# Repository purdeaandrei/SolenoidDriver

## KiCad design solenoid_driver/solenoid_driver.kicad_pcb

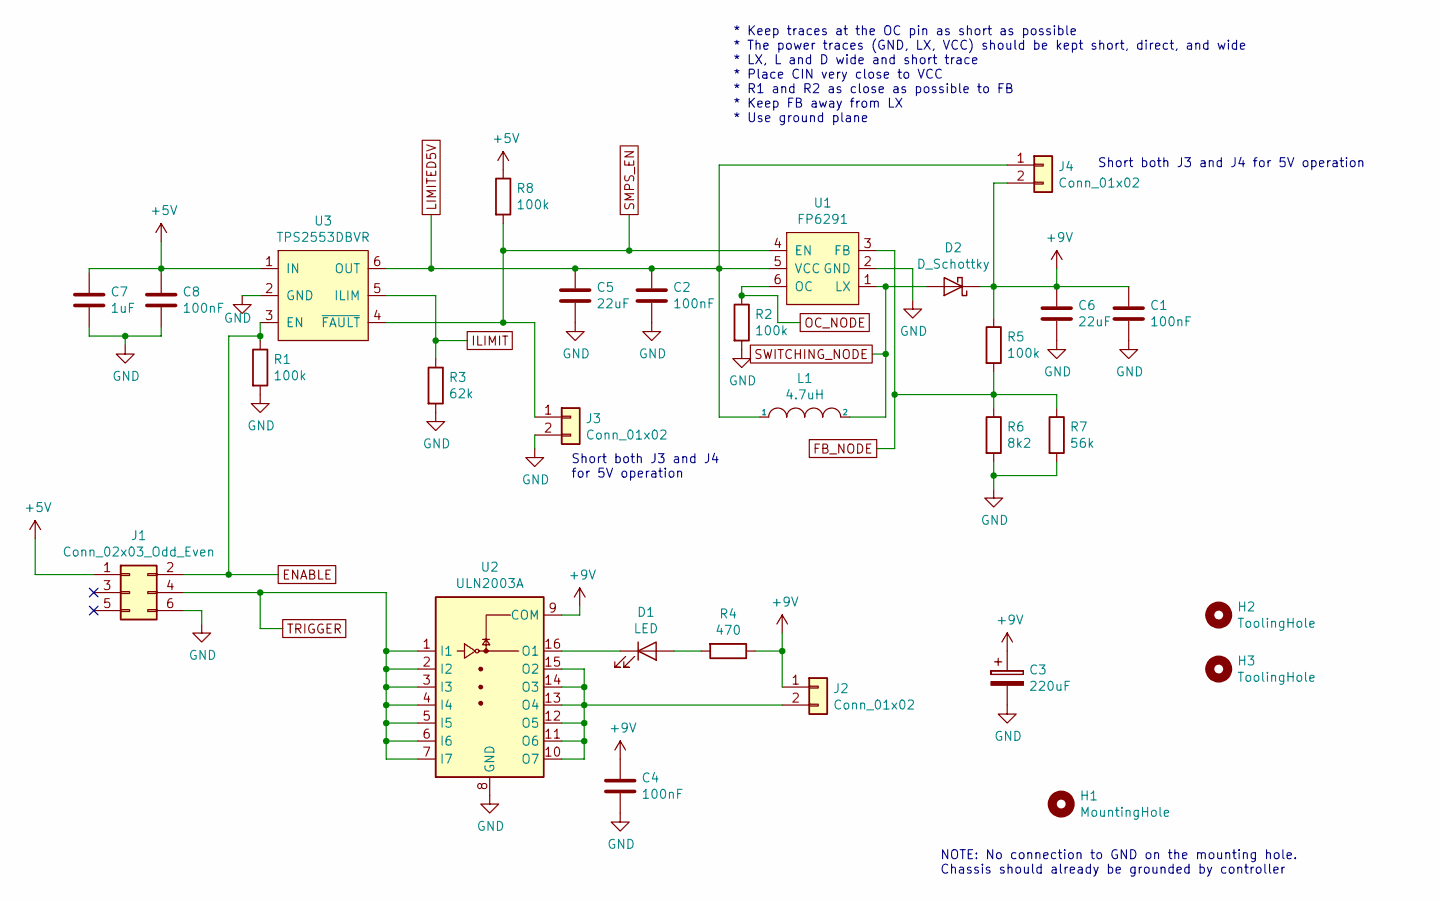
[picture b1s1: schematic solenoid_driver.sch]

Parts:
C1, C2, C4, C8: 100nF; C_0805_2012Metric_Pad1.15x1.40mm_HandSolder; LCSC C49678
C3: 220uF; CP_Elec_6.3x7.7; LCSC C127327
C5, C6: 22uF; C_0805_2012Metric_Pad1.15x1.40mm_HandSolder; LCSC C45783
C7: 1uF; C_0805_2012Metric_Pad1.15x1.40mm_HandSolder; LCSC C28323
D1: LED; LED_0805_2012Metric_Pad1.15x1.40mm_HandSolder; LCSC C2296
D2: D_Schottky; D_SMA; LCSC C2480
H1: MountingHole; MountingHole_4mm_Pad
H2, H3: ToolingHole; tooling_hole
J1: Conn_02x03_Odd_Even; PinHeader_2x03_P2.54mm_Vertical
J2: Conn_01x02; PinHeader_1x02_P2.54mm_Vertical
J3, J4: Conn_01x02; shortable
L1: 4.7uH; footprint_for_MWSA0402_HANDSOLD; LCSC C408337
R1, R2, R5, R8: 100k; R_0805_2012Metric_Pad1.15x1.40mm_HandSolder; LCSC C17407
R3: 62k; R_0805_2012Metric_Pad1.15x1.40mm_HandSolder; LCSC C17783
R4: 470; R_0805_2012Metric_Pad1.15x1.40mm_HandSolder; LCSC C17710
R6: 8k2; R_0805_2012Metric_Pad1.15x1.40mm_HandSolder; LCSC C17828
R7: 56k; R_0805_2012Metric_Pad1.15x1.40mm_HandSolder; LCSC C17756
U1: FP6291; SOT-23-6_Handsoldering; LCSC C18701
U2: ULN2003A; SOIC-16_3.9x9.9mm_P1.27mm; LCSC C7512
U3: TPS2553DBVR; SOT-23-6_Handsoldering; LCSC C55266

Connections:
+5V: C7.1, C8.1, J1.1, R8.1, U3.1 (IN)
+9V: C1.1, C3.1, C4.1, C6.1, D2.1 (K), J2.1, J4.2, R4.1, R5.1, U2.9 (COM)
ENABLE: J1.2, R1.1, U3.3 (EN)
FB_NODE: R5.2, R6.1, R7.1, U1.3 (FB)
GND: C1.2, C2.2, C3.2, C4.2, C5.2, C6.2, C7.2, C8.2, J1.6, J3.2, R1.2, R2.2, R3.2, R6.2, R7.2, U1.2 (GND), U2.8 (GND), U3.2 (GND)
ILIMIT: R3.1, U3.5 (ILIM)
LIMITED5V: C2.1, C5.1, J4.1, L1.1, U1.5 (VCC), U3.6 (OUT)
unnamed: D1.1 (K), U2.16 (O1)
unnamed: D1.2 (A), R4.2
unnamed: J2.2, U2.10 (O7), U2.11 (O6), U2.12 (O5), U2.13 (O4), U2.14 (O3), U2.15 (O2)
OC_NODE: R2.1, U1.6 (OC)
SMPS_EN: J3.1, R8.2, U1.4 (EN), U3.4 (~FAULT)
SWITCHING_NODE: D2.2 (A), L1.2, U1.1 (LX)
TRIGGER: J1.4, U2.1 (I1), U2.2 (I2), U2.3 (I3), U2.4 (I4), U2.5 (I5), U2.6 (I6), U2.7 (I7)

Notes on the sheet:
* Keep traces at the OC pin as short as possible * The power traces (GND, LX, VCC) should be kept short, direct, and wide * LX, L and D wide and short trace * Place CIN very close to VCC * R1 and R2 as close as possible to FB * Keep FB away from LX * Use ground plane
NOTE: No connection to GND on the mounting hole. Chassis should already be grounded by controller
Short both J3 and J4 for 5V operation
Short both J3 and J4 for 5V operation

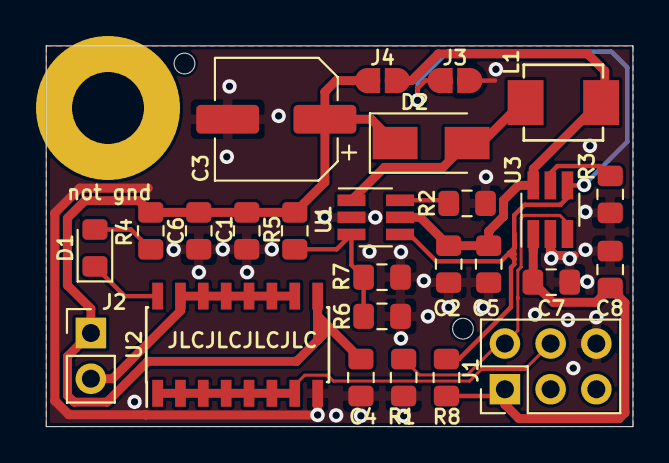
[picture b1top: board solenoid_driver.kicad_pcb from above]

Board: 2 copper layers, 32.6 x 21.1 mm, 29 parts (0 on the bottom side), 14 nets.

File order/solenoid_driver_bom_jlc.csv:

"Comment","Designator","Footprint","LCSC Part #"
"100nF","C2,C4,C1,C8","C_0805_2012Metric_Pad1.15x1.40mm_HandSolder","C49678"
"220uF","C3","CP_Elec_6.3x7.7","C127327"
"22uF","C5,C6","C_0805_2012Metric_Pad1.15x1.40mm_HandSolder","C45783"
"1uF","C7","C_0805_2012Metric_Pad1.15x1.40mm_HandSolder","C28323"
"LED","D1","LED_0805_2012Metric_Pad1.15x1.40mm_HandSolder","C2296"
"D_Schottky","D2","D_SMA","C2480"
"4.7uH","L1","footprint_for_MWSA0402_HANDSOLD","C408337"
"100k","R1,R5,R2,R8","R_0805_2012Metric_Pad1.15x1.40mm_HandSolder","C17407"
"62k","R3","R_0805_2012Metric_Pad1.15x1.40mm_HandSolder","C17783"
"470","R4","R_0805_2012Metric_Pad1.15x1.40mm_HandSolder","C17710"
"8k2","R6","R_0805_2012Metric_Pad1.15x1.40mm_HandSolder","C17828"
"56k","R7","R_0805_2012Metric_Pad1.15x1.40mm_HandSolder","C17756"
"FP6291","U1","SOT-23-6_Handsoldering","C18701"
"ULN2003A","U2","SOIC-16_3.9x9.9mm_P1.27mm","C7512"
"TPS2553DBVR","U3","SOT-23-6_Handsoldering","C55266"

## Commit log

2020-11-01 added version 1.0b with alternative inductor, because the inductor used by version 1.0 is low on stock. This variant has not been tested.
2020-11-01 Use handsoldered footprint, add 3d model
2022-07-31 Updated 100k resistor part reference
2022-07-31 Updated 22uF capacitor part reference
2022-07-31 Updated 100k resistor and 22uF capacitor part references
